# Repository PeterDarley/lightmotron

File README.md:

# Lightmotron

A lighting controller for plastic model kits, running on an ESP32-S3. Uses
NeoPixel LED strips to produce dynamic lighting effects, with optional MP3
sound playback — all configured and controlled from a web interface over
WiFi, no app or account required.

## License

You are welcome to use this project in products, research, kits, and services.
Selling the software itself, or minor variations of it, as a standalone product is against the spirit of the project.

```
This software is licensed under GPLv3 with the following additional permission:
You may sell products or services that include this software, provided the software is not sold independently.
Distribution of the software itself, except as part of a larger product or service, is not permitted.
```

## Features

* NeoPixel LED strip control with 15 built-in animation patterns and 11 post-processing filters
* Combine effects into named **scenes**, triggered manually or automatically
* Optional MP3 sound playback (looping, chaining, soundscapes) synced to scenes
* Multiple named **Models**, for controlling more than one kit from a single device
* Browser-based control interface — no app install required
* WiFi connectivity with a guided first-time setup (captive portal)
* Firmware updates over WiFi, right from the web interface

## Install

**[peterdarley.github.io/lightmotron](https://peterdarley.github.io/lightmotron/)**
— flashes the firmware directly from your browser over USB. No drivers,
no command line, no account.

1. Connect your ESP32-S3 board to your computer with a USB-C **data**
   cable (not a charge-only cable).
2. Open the link above in **Google Chrome** or **Microsoft Edge** (this
   uses the [Web Serial API](https://developer.chrome.com/docs/capabilities/serial),
   which only those browsers support).
3. Click **Install Lightmotron** and select your device's serial port when
   prompted.

That's it — the page writes everything a blank board needs. Once it's
done, unplug the USB cable (or leave it connected for power) and continue
to [First Boot](#first-boot--wifi-setup) below.

Already have a Lightmotron device and just want to update it? Use
**Setup → Updates** in the web interface instead — see
[Firmware Updates](#firmware-updates) below.

## Hardware

* **Microcontroller**: YD-ESP32-S3 board (ESP32-S3-WROOM-1 N16R8 module —
  16MB flash, 8MB octal PSRAM)
* **Lighting**: a NeoPixel-compatible LED strip (default GPIO 4;
  configurable in System Settings) — see the
  [NeoPixel Wiring Diagram](docs/neopixel-wiring.md)
* **Sound (optional)**: up to 3 YX5200-based MP3 player modules with a
  small amplifier and speakers — see the [Hardware Reference](docs/hardware.md)

## First Boot — WiFi Setup

On first boot (or whenever WiFi credentials are missing or fail to connect), the device starts a **captive portal** access point:

1. Look for a WiFi network called **`lightmotron-setup`** on your phone or laptop and connect to it.
2. Your device should automatically open the portal page. If not, navigate to `http://192.168.4.1/`.
3. The page shows a list of nearby WiFi networks sorted by signal strength. Select yours, enter the password, then tap **Save & Connect**. If your network isn't listed, choose **Other** to enter the SSID manually, or use the **rescan** link if you don't see it yet.
4. The device reboots and joins your network. You can then access it at `http://lightmotron.local/` (or `http://<hostname>.local/` if you've set a custom hostname). If `.local` addresses don't resolve on your network (common on Android), try `http://lightmotron.lan/`, `http://lightmotron.home/`, or just `http://lightmotron/`.

SSID matching is case-insensitive, so credentials stored with different capitalization will still connect.

Credentials are stored persistently, so this only needs to be done once. To change them later, use **System Settings** on the Setup page.

## Web Interface

Once the device is on your network, open its address in a browser.

### Home Page

Control animation playback and trigger scenes from here day-to-day: start/stop the lighting engine, switch between scenes, play sounds and soundscapes. The Active Scenes list shows both ongoing scenes and any immediate (one-shot trigger) scenes while they're running.

### Setup Page

Configure everything: custom colors, named LED ranges, effects, filters, scenes, sounds, soundscapes, models, and the interface theme. See the **[Programming Guide](docs/programming.md)** for a complete walkthrough of every option and what it does.

System Settings on this page also covers WiFi credentials, hostname, NeoPixel strip wiring, and audio module pin assignments — changes there take effect on the next reboot.

**IP address announcement**: if audio modules are configured and the device's IP address has changed since it last booted, it announces the new address by voice automatically (each octet's digits, repeated once after 15 seconds). Use **Mark Current IP as Announced** on the Setup page if you don't want to hear it again for the current address.

### Status Page

Monitor system health: memory and storage usage, networking details, animation state, the reason for the last reboot, and the responsiveness of any configured audio modules. Download or restore your entire configuration as a JSON backup file from here — restoring never overwrites WiFi credentials, so a backup is safe to move between devices.

### Storage Page

View the raw JSON configuration underlying everything else on the device, for advanced inspection or manual editing. WiFi passwords are masked as `***` here for safety.

## Firmware Updates

Setup → Updates checks the configured GitHub repository (defaults to this
one) for a newer release and, when you confirm, downloads and installs it
— no cable required. Your settings, scenes, and sounds are untouched by an
update; only the firmware itself changes.

## History

Lightmotron began as a MicroPython project. It's since been fully rewritten in C for better performance and reliability, and that's what you'll get from the installer above — the original MicroPython version is no longer maintained. If you're curious about the internals or want to build the firmware yourself, see the [Developer Guide](docs/developer.md).

## Documentation

* **[Programming Guide](docs/programming.md)** — how to configure effects, filters, sounds, and scenes
* **[Developer Guide](docs/developer.md)** — architecture, building from source, and links to the rest of the technical docs

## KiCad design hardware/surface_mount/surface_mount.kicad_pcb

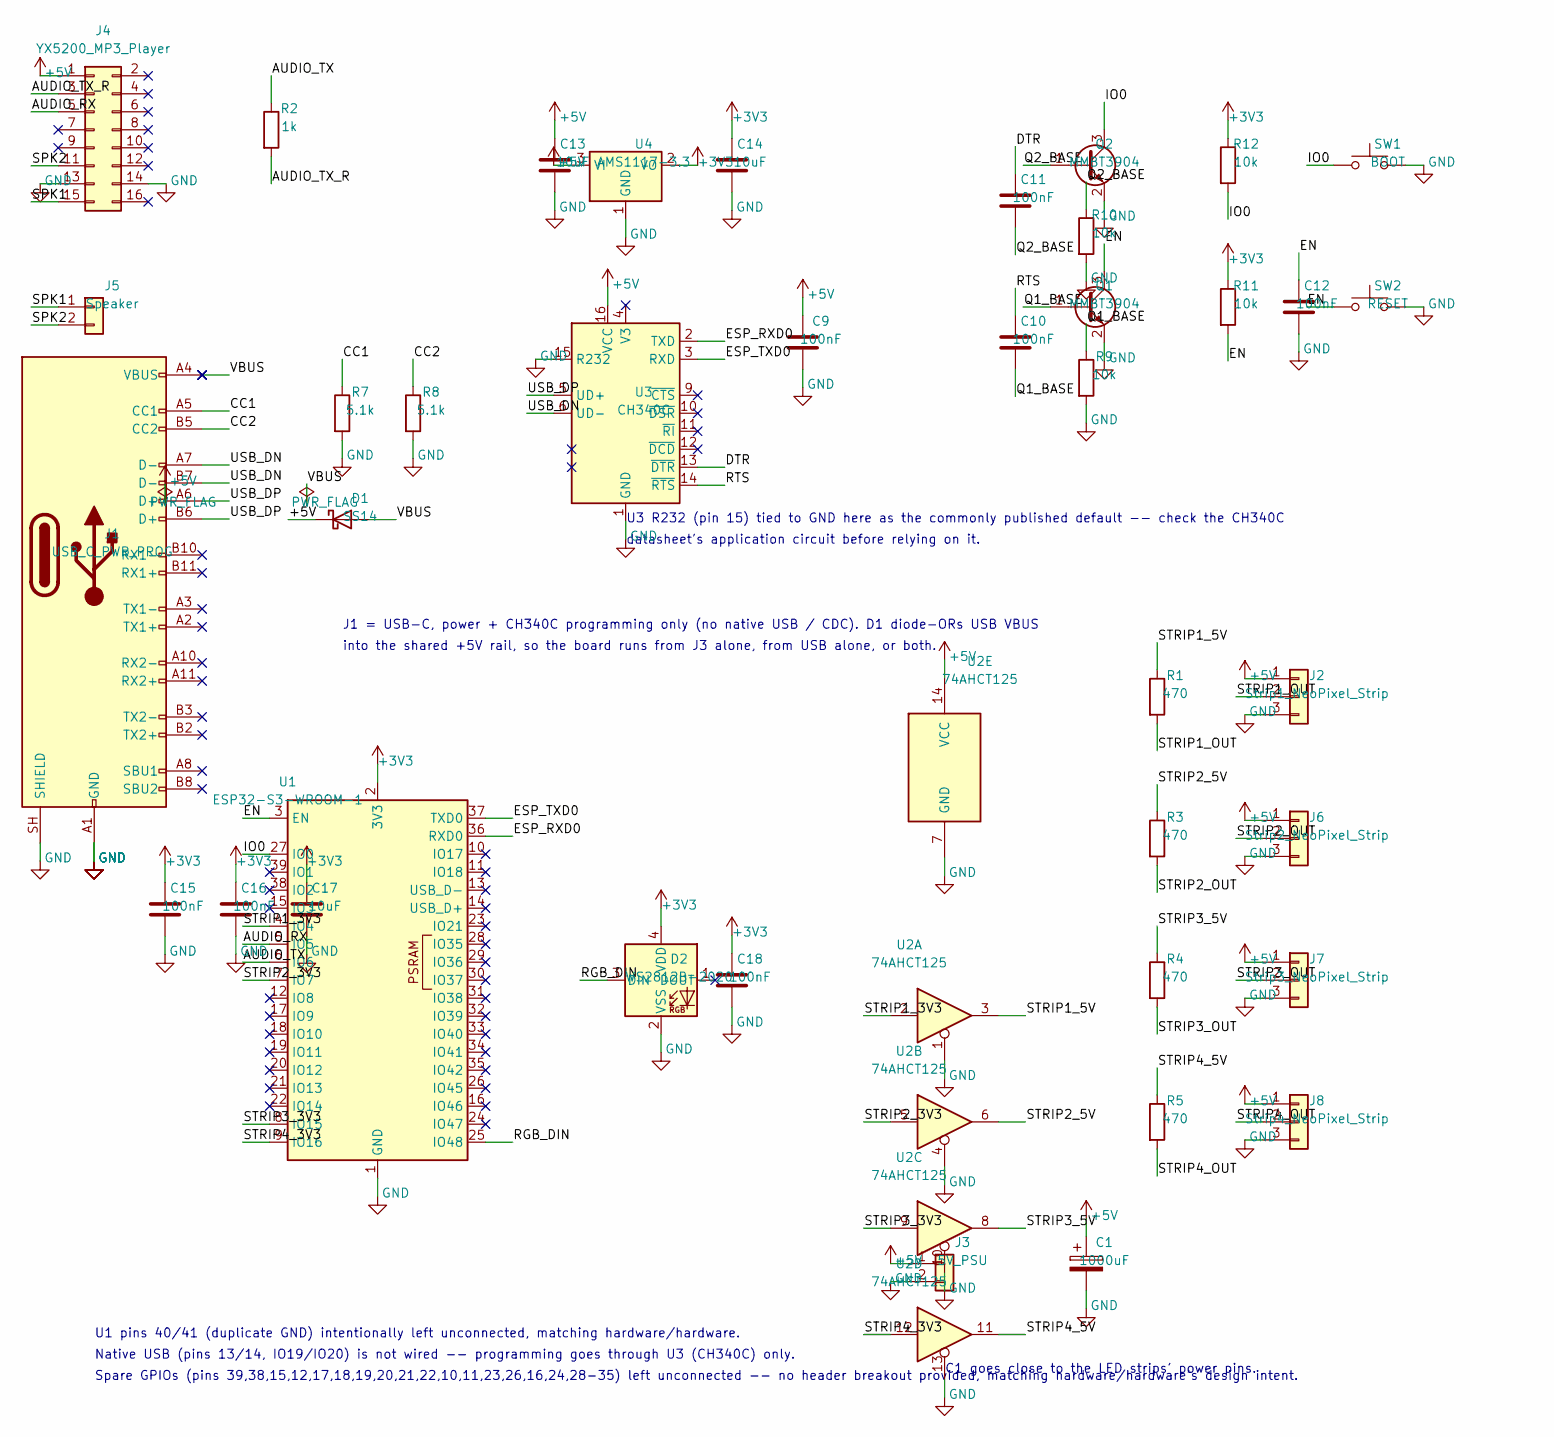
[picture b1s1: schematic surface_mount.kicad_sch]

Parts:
C1: 1000uF; CP_Elec_10x10.5
C9, C10, C11, C12, C15, C16, C18: 100nF; C_0603_1608Metric
C13, C14, C17: 10uF; C_0805_2012Metric
D1: SS14; D_SOD-123
D2: WS2812B-2020; LED_WS2812B-2020_PLCC4_2.0x2.0mm
J1: USB_C_PWR_PROG; USB_C_Receptacle_Amphenol_12401548E4-2A
J2: Strip1_NeoPixel_Strip; PinHeader_1x03_P2.54mm_Vertical
J3: 5V_PSU; PinHeader_1x02_P2.54mm_Vertical
J4: YX5200_MP3_Player; YX5200_DFPlayer_DIP16_W15.24mm
J5: Speaker; PinHeader_1x02_P2.54mm_Vertical
J6: Strip2_NeoPixel_Strip; PinHeader_1x03_P2.54mm_Vertical
J7: Strip3_NeoPixel_Strip; PinHeader_1x03_P2.54mm_Vertical
J8: Strip4_NeoPixel_Strip; PinHeader_1x03_P2.54mm_Vertical
Q1, Q2: MMBT3904; SOT-23
R1, R3, R4, R5: 470; R_0805_2012Metric
R2: 1k; R_0805_2012Metric
R7, R8: 5.1k; R_0805_2012Metric
R9, R10, R11, R12: 10k; R_0805_2012Metric
SW1: BOOT; Panasonic_EVQPUJ_EVQPUA
SW2: RESET; Panasonic_EVQPUJ_EVQPUA
U1: ESP32-S3-WROOM-1
U2: 74AHCT125; SOIC-14_3.9x8.7mm_P1.27mm
U3: CH340C; SOIC-16_3.9x9.9mm_P1.27mm
U4: AMS1117-3.3; SOT-223-3_TabPin2

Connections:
+3V3: C14.1, C15.1, C16.1, C17.1, C18.1, D2.4 (VDD), R11.1, R12.1, U1.2 (3V3), U4.2 (VO)
/AUDIO_RX: J4.5, U1.5 (IO5)
/AUDIO_TX: R2.1, U1.6 (IO6)
/AUDIO_TX_R: J4.3, R2.2
/CC1: J1.A5 (CC1), R7.1
/CC2: J1.B5 (CC2), R8.1
/DTR: C11.1, U3.13 (~DTR)
/EN: C12.1, Q1.3 (C), R11.2, SW2.1, U1.3 (EN)
/ESP_RXD0: U1.36 (RXD0), U3.2 (TXD)
/ESP_TXD0: U1.37 (TXD0), U3.3 (RXD)
/IO0: Q2.3 (C), R12.2, SW1.1, U1.27 (IO0)
/Q1_BASE: C10.2, Q1.1 (B), R9.1
/Q2_BASE: C11.2, Q2.1 (B), R10.1
/RGB_DIN: D2.3 (DIN), U1.25 (IO48)
/RTS: C10.1, U3.14 (~RTS)
/SPK1: J4.15, J5.1
/SPK2: J4.11, J5.2
/STRIP1_3V3: U1.4 (IO4), U2.2
/STRIP1_5V: R1.1, U2.3
/STRIP1_OUT: J2.2, R1.2
/STRIP2_3V3: U1.7 (IO7), U2.5
/STRIP2_5V: R3.1, U2.6
/STRIP2_OUT: J6.2, R3.2
/STRIP3_3V3: U1.8 (IO15), U2.9
/STRIP3_5V: R4.1, U2.8
/STRIP3_OUT: J7.2, R4.2
/STRIP4_3V3: U1.9 (IO16), U2.12
/STRIP4_5V: R5.1, U2.11
/STRIP4_OUT: J8.2, R5.2
/USB_DN: J1.A7 (D-), J1.B7 (D-), U3.6 (UD-)
/USB_DP: J1.A6 (D+), J1.B6 (D+), U3.5 (UD+)
GND: C1.2, C9.2, C12.2, C13.2, C14.2, C15.2, C16.2, C17.2, C18.2, D2.2 (VSS), J1.A1 (GND), J1.A12 (GND), J1.B1 (GND), J1.B12 (GND), J1.SH (SHIELD), J2.3, J3.2, J4.13, J4.14, J6.3, J7.3, J8.3, Q1.2 (E), Q2.2 (E), R7.2, R8.2, R9.2, R10.2, SW1.2, SW2.2, U1.1 (GND), U1.40 (GND), U1.41 (GND), U2.1, U2.4, U2.7 (GND), U2.10, U2.13, U3.1 (GND), U3.15 (R232), U4.1 (GND)

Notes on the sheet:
J1 = USB-C, power + CH340C programming only (no native USB / CDC). D1 diode-ORs USB VBUS
into the shared +5V rail, so the board runs from J3 alone, from USB alone, or both.
U3 R232 (pin 15) tied to GND here as the commonly published default -- check the CH340C
datasheet's application circuit before relying on it.
U1 pins 40/41 (duplicate GND) intentionally left unconnected, matching hardware/hardware.
Native USB (pins 13/14, IO19/IO20) is not wired -- programming goes through U3 (CH340C) only.
Spare GPIOs (pins 39,38,15,12,17,18,19,20,21,22,10,11,23,26,16,24,28-35) left unconnected -- no header breakout provided, matching hardware/hardware's design intent.
C1 goes close to the LED strips' power pins.

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
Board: 2 copper layers, 36 parts (0 on the bottom side), 26 nets, no tracks yet.

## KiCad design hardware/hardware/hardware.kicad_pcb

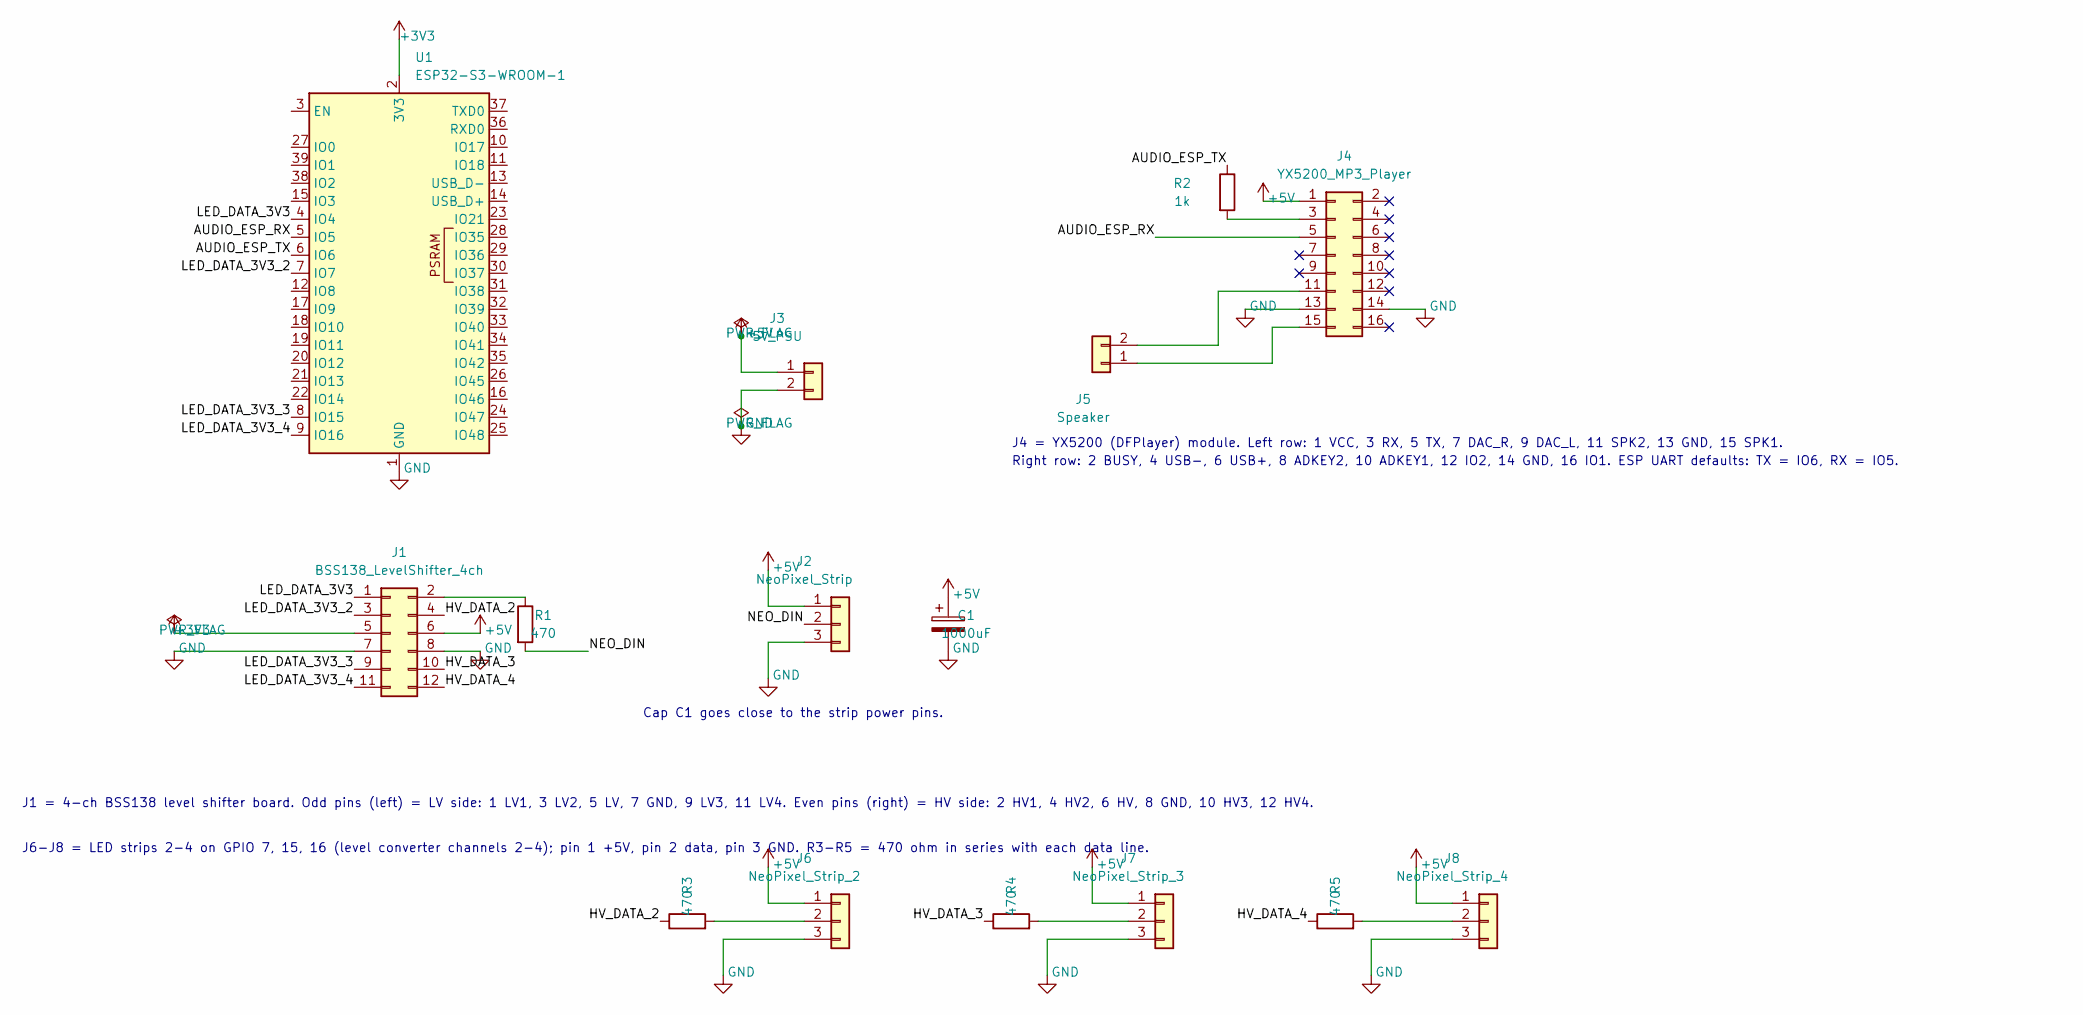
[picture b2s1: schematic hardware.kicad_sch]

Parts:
C1: 1000uF; CP_Radial_D10.0mm_P5.00mm
J1: BSS138_LevelShifter_4ch; BSS138_LevelShifter_4ch_2x06_P2.54mm_Row10.16mm
J2: NeoPixel_Strip; PinHeader_1x03_P2.54mm_Vertical
J3: 5V_PSU; PinHeader_1x02_P2.54mm_Vertical
J4: YX5200_MP3_Player; YX5200_DFPlayer_DIP16_W15.24mm
J5: Speaker; PinHeader_1x02_P2.54mm_Vertical
J6: NeoPixel_Strip_2; PinHeader_1x03_P2.54mm_Vertical
J7: NeoPixel_Strip_3; PinHeader_1x03_P2.54mm_Vertical
J8: NeoPixel_Strip_4; PinHeader_1x03_P2.54mm_Vertical
R1, R3, R4, R5: 470; R_Axial_DIN0207_L6.3mm_D2.5mm_P10.16mm_Horizontal
R2: 1k; R_Axial_DIN0207_L6.3mm_D2.5mm_P10.16mm_Horizontal
U1: ESP32-S3-WROOM-1; YD-ESP32-S3_DevKit_2x22_P2.54mm

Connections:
+3V3: J1.5, U1.2 (3V3)
+5V: C1.1, J1.6, J2.1, J3.1, J4.1, J6.1, J7.1, J8.1
/AUDIO_ESP_RX: J4.5, U1.5 (IO5)
/AUDIO_ESP_TX: R2.1, U1.6 (IO6)
/HV_DATA_2: J1.4, R3.1
/HV_DATA_3: J1.10, R4.1
/HV_DATA_4: J1.12, R5.1
/LED_DATA_3V3: J1.1, U1.4 (IO4)
/LED_DATA_3V3_2: J1.3, U1.7 (IO7)
/LED_DATA_3V3_3: J1.9, U1.8 (IO15)
/LED_DATA_3V3_4: J1.11, U1.9 (IO16)
/NEO_DIN: J2.2, R1.2
GND: C1.2, J1.7, J1.8, J2.3, J3.2, J4.13, J4.14, J6.3, J7.3, J8.3, U1.1 (GND), U1.40 (GND), U1.41 (GND)
unnamed: J1.2, R1.1
unnamed: J4.3, R2.2
unnamed: J4.11, J5.2
unnamed: J4.15, J5.1
unnamed: J6.2, R3.2
unnamed: J7.2, R4.2
unnamed: J8.2, R5.2

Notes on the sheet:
J1 = 4-ch BSS138 level shifter board. Odd pins (left) = LV side: 1 LV1, 3 LV2, 5 LV, 7 GND, 9 LV3, 11 LV4. Even pins (right) = HV side: 2 HV1, 4 HV2, 6 HV, 8 GND, 10 HV3, 12 HV4.
Cap C1 goes close to the strip power pins.
J4 = YX5200 (DFPlayer) module. Left row: 1 VCC, 3 RX, 5 TX, 7 DAC_R, 9 DAC_L, 11 SPK2, 13 GND, 15 SPK1.
Right row: 2 BUSY, 4 USB-, 6 USB+, 8 ADKEY2, 10 ADKEY1, 12 IO2, 14 GND, 16 IO1. ESP UART defaults: TX = IO6, RX = IO5.
J6-J8 = LED strips 2-4 on GPIO 7, 15, 16 (level converter channels 2-4); pin 1 +5V, pin 2 data, pin 3 GND. R3-R5 = 470 ohm in series with each data line.

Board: 2 copper layers, 15 parts (0 on the bottom side), 20 nets, no tracks yet.

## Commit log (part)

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2026-03-22 Initial copy in from ThinkTank
2026-03-22 Update submodule configuration for micropython_common_libraries
2026-03-22 Refactor web structure: remove TestView, add HomeView and initialize routes
2026-03-22 Update README and scripts: revise project description, enhance upload script for directory handling
2026-03-22 Implement animation controls and scene selection: add buttons for starting/stopping animations and selecting scenes
2026-03-27 Add navigation bar and setup/storage pages; implement StorageView and SetupView
2026-03-27 Add status and LED picker views; enhance setup page with LED naming functionality
2026-03-27 Add .playwright-mcp/ to .gitignore to exclude Playwright-related files
2026-03-27 Add playwright to requirements.txt
2026-03-27 Add Playwright configuration to VSCode settings
2026-03-27 Refactor LED naming functionality with new toggle and clear routes; update setup and LED picker templates for improved interaction
2026-03-27 Add clarification on shared lib directory usage in Copilot instructions
2026-03-28 Add subproject reference for library integration
2026-04-01 Update default COM port from COM3 to COM4 in REPL and upload scripts; add new binary files for ESP32 and update documentation images.
2026-04-01 Update subproject reference to latest commit e7504e4
2026-04-01 Enhance status and storage views: format memory and storage metrics, add JSON rendering for storage data
2026-04-01 Update subproject reference to latest commit df552c0
2026-04-01 Implement LED range editing functionality: add NamedRangeEditView, update routes, and create led_picker_edit.html template
2026-04-01 Refactor LED picker functionality: consolidate JavaScript logic into led_picker.js, enhance user instructions in setup.html, and add NamedRangeSetView for managing LED selections.
2026-04-04 Update subproject reference to latest commit 37127ce5
2026-04-04 Add favicon SVG file and include it in base_head.html
2026-04-05 Update subproject reference to latest commit bcb6b5e
2026-04-05 Update subproject reference to latest commit d901486
2026-04-05 Update page title in base_head.html to include dynamic page_title
2026-04-06 Add test color to lighting system
2026-04-06 Mark custom colors setup task as completed in todo list
2026-04-07 Update subproject reference to latest commit d99baad
2026-04-07 Add custom colors management feature with UI and backend integration
2026-04-09 Refactor delete button for custom colors to use htmx for better interaction
2026-04-10 Enhance custom templating system documentation with feature usage details
2026-04-10 Add scenes management feature with UI and backend integration
2026-04-10 Update target parameter format in pattern_params.html and improve error handling in StorageView
2026-04-10 Update subproject reference to latest commit 739619f
2026-04-10 Update subproject reference to latest commit 6a0900e
2026-04-10 Add color selection functionality and enhance custom colors management
2026-04-10 Update subproject reference to latest commit 783f3c0
2026-04-16 Clarify instructions on running Python locally and remove unnecessary examples
2026-04-16 Enhance frequency parameter input with slider and number input; sort scenes and named ranges in context
2026-04-16 Refactor setup page layout with cards for named ranges, custom colors, and scenes; add summary views for each section
2026-04-16 Add guideline for CSS file organization; prohibit inline styles in templates
2026-04-16 Update subproject reference to latest commit 4473d18
2026-04-16 Implement effects management: add effects overview, editing, and summary features
2026-04-16 Update subproject reference to latest commit f57239f
2026-04-18 Update subproject reference to latest commit 57c6884
2026-04-18 Enhance templating instructions: add support for membership tests and logical connectives in conditionals
2026-04-18 Add lighting filter design guidelines to Copilot instructions
2026-04-18 Update subproject reference to latest commit 5a11f15
2026-04-18 Refactor optional parameters: replace frequency with duration and period settings in pattern parameters template
2026-04-18 Add 'After' and 'Inherit Target' fields to scene entry form and context
2026-04-20 Update subproject reference to latest commit 0d08db3
2026-04-20 Update subproject reference to latest commit 6115f14
2026-04-20 Add theming documentation for the home page
2026-04-20 Implement theming support: add theme classes to buttons and panels, create theme context processor, and add theme selection functionality
2026-04-20 Adjust padding for body and sections in LCARS theme for improved layout
2026-04-20 Refactor storage template layout and add Klingon theme styles
2026-04-20 Update subproject reference to latest commit
2026-04-20 Add CSS nesting guidelines to copilot instructions
2026-04-20 Add single LEDs image to documentation
2026-04-21 Add Star Wars themes: Imperial and Rebel styles, and new sound file
2026-04-21 Add .upload_manifest.json to .gitignore
2026-04-21 Enhance upload script to support incremental uploads with -Force option and improved file change detection
2026-04-21 Refactor code structure for improved readability and maintainability
2026-04-21 Enhance README.md with web interface details and new phaser_strip effect documentation
2026-04-21 Update README.md to enhance lighting system documentation and add web interface usage details; create internals.md for technical specifications of patterns and filters
2026-04-21 Update submodule to latest commit for improved functionality
2026-04-21 Enhance README.md with detailed web interface documentation, including Home, Setup, Status, and Storage pages, along with custom colors, named ranges, filters, effects, scenes, and theme options.
2026-04-23 Update copilot instructions to emphasize keeping documentation in sync with code changes
2026-04-23 Implement system settings management with WiFi credentials, hostname, and NeoPixel configuration; add UI for editing and displaying settings.
2026-04-23 Add littlefs-python to requirements.txt for enhanced functionality
2026-04-23 Add web installer and firmware manifest for Lightmotron
2026-04-26 Update subproject reference in lib directory
2026-04-26 Add serial port selection feature to installation page
2026-04-26 Remove outdated binary files and update manifest with new firmware source; enhance serial port selection and installation process in index.html
2026-05-04 Enhance robustness of scene label construction and audio player configuration; handle non-string entries and missing values gracefully
2026-05-11 Add instructions for using a logic level converter with ESP32-S3 and MAX7219
2026-05-11 Refactor parameter handling in pattern_params.html and enhance type hints in views.py
2026-05-16 Implement OTA update functionality and UI for managing updates from GitHub
2026-05-16 Add tracked files and submodule support documentation
2026-05-16 Enhance OTA update functionality with submodule tracking and debug logging support
2026-05-16 Refine tracked and excluded paths for OTA updates in documentation and code
2026-05-17 Add Event Horizon theme with dark sci-fi style and custom CSS variables
2026-05-17 Add delayed reset functionality after successful updates in UpdatesView
2026-05-20 Refactor LED picker and named range handling; enhance UI and server sync
2026-05-21 Update subproject reference to latest commit efbb091
2026-05-21 Enhance effect and filter management UI; add dynamic filter display and color contrast for named ranges
2026-05-21 Implement copy functionality for storage content; enhance button feedback and fallback mechanism
2026-05-21 Update subproject reference to latest commit 97935fc
2026-05-21 Add detailed lighting module layout section to internals documentation
2026-05-22 Enhance effect editor with optional settings and improved slider styles; update scene reference handling in UI
2026-05-22 Update subproject reference to latest commit 4ab8a8a
2026-05-23 Add input group text styles for various themes
2026-05-23 Update subproject reference to latest commit 2865d67
2026-05-23 Update subproject reference to latest commit c9a86bd
2026-05-23 Enhance audio features: implement sound playback controls, add audio reset on boot, and improve upload script with retry logic
2026-05-23 Update subproject reference to latest commit 45876e12
2026-05-23 Enhance audio features: improve upload process with mpremote resume mode, ensure critical runtime files are recopied during uploads, and add audio debug logging options. Update sound management UI fo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
2026-05-23 Update subproject reference to latest commit 49342c2
2026-05-23 Update subproject reference to latest commit 157b722
2026-05-23 Refactor boot process: remove unused I2CManager import, optimize PersistentDict usage for system settings and WiFi credentials retrieval. Add utility function to normalize form values into a list in 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
2026-05-24 Enhance documentation and UI for sound and scene management
    - Updated README.md to include new scene-level behaviors and status page details.
    - Modified boot.py to initiate continuous audio polling during boot.
    - Expanded internals.md with detailed audio diagnostics and new sound playback features.
    - Updated settings_template.py to include new sound properties: loop, stops, and next_sound.
    - Refined models.html for better sound management UI, including edit and delete options.
    - Enhanced scene_edit.html to allow stopping sounds on scene start and end.
2026-05-27 Update subproject reference to latest commit d32286a
2026-05-27 Enhance documentation and styling for LCARS theme, update upload script for content change detection, and improve animation state handling in views
2026-05-28 Update build_deployment.py to set default filesystem size for ESP32-S3 and improve error handling
2026-05-28 Add Soundscapes section to README with details on creating and managing sound entries
2026-05-28 Add note on settings editability through the UI
2026-05-28 Enhance soundscape management: add editing capabilities, metadata display, and repeat settings
2026-05-28 chore: Update subproject reference to latest commit dfc20eb
2026-05-28 docs: Update README and internals documentation for soundscape and home controls enhancements
2026-05-28 feat: Enhance soundscape editing and volume control features
2026-05-31 feat: Improve sound stopping functionality and error handling in StopSoundView
2026-05-31 Duplicated lightmotron in C
2026-06-01 docs: Update hardware specifications and add image for YD-ESP32-S3 board
2026-06-01 feat: Enhance error handling and resource management in various components
2026-06-14 Removed unneeded image
2026-06-14 Added sounds to alert the user if the IP address changes
